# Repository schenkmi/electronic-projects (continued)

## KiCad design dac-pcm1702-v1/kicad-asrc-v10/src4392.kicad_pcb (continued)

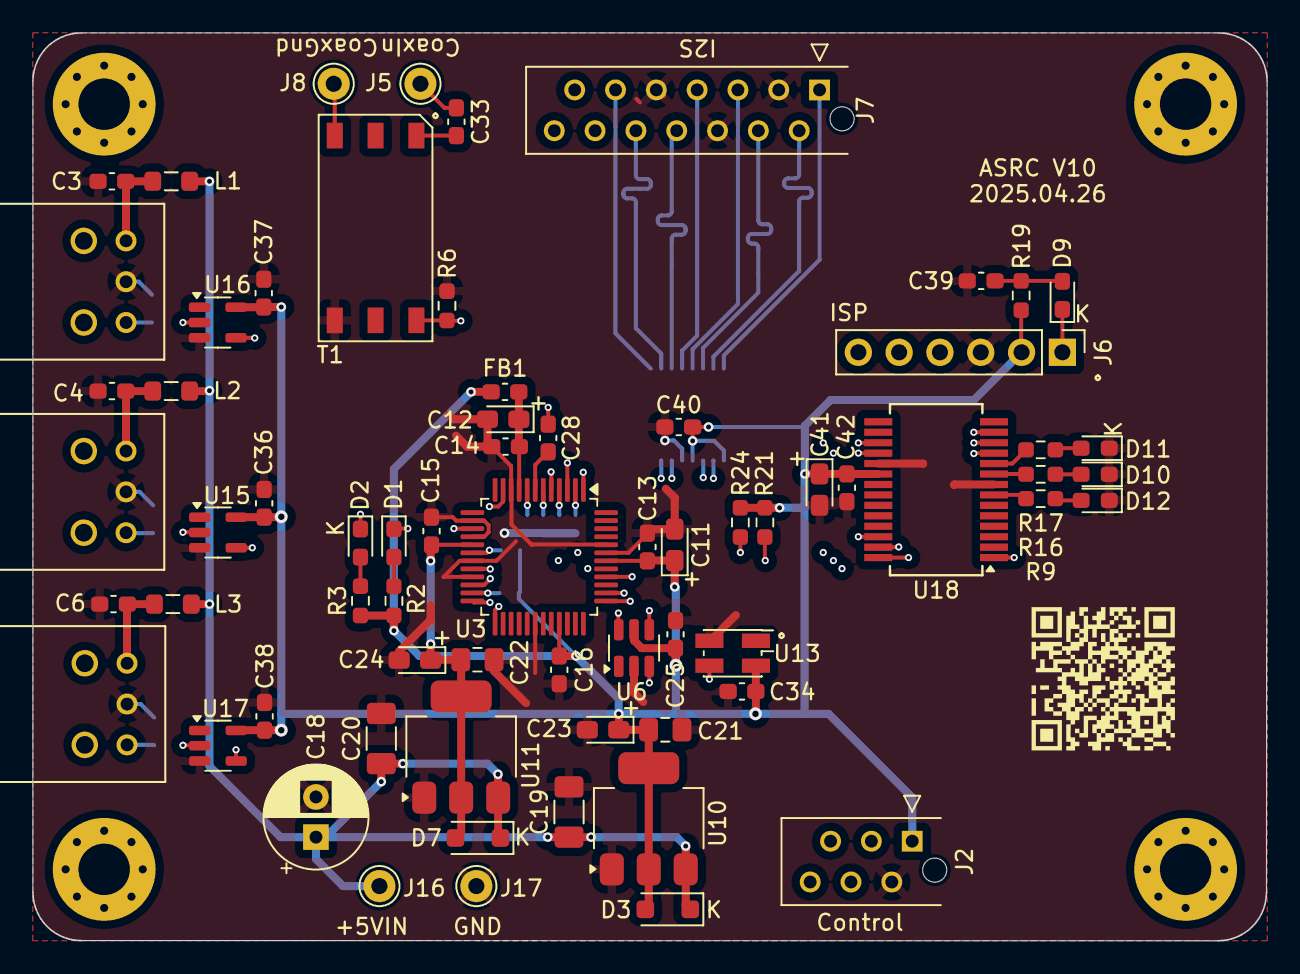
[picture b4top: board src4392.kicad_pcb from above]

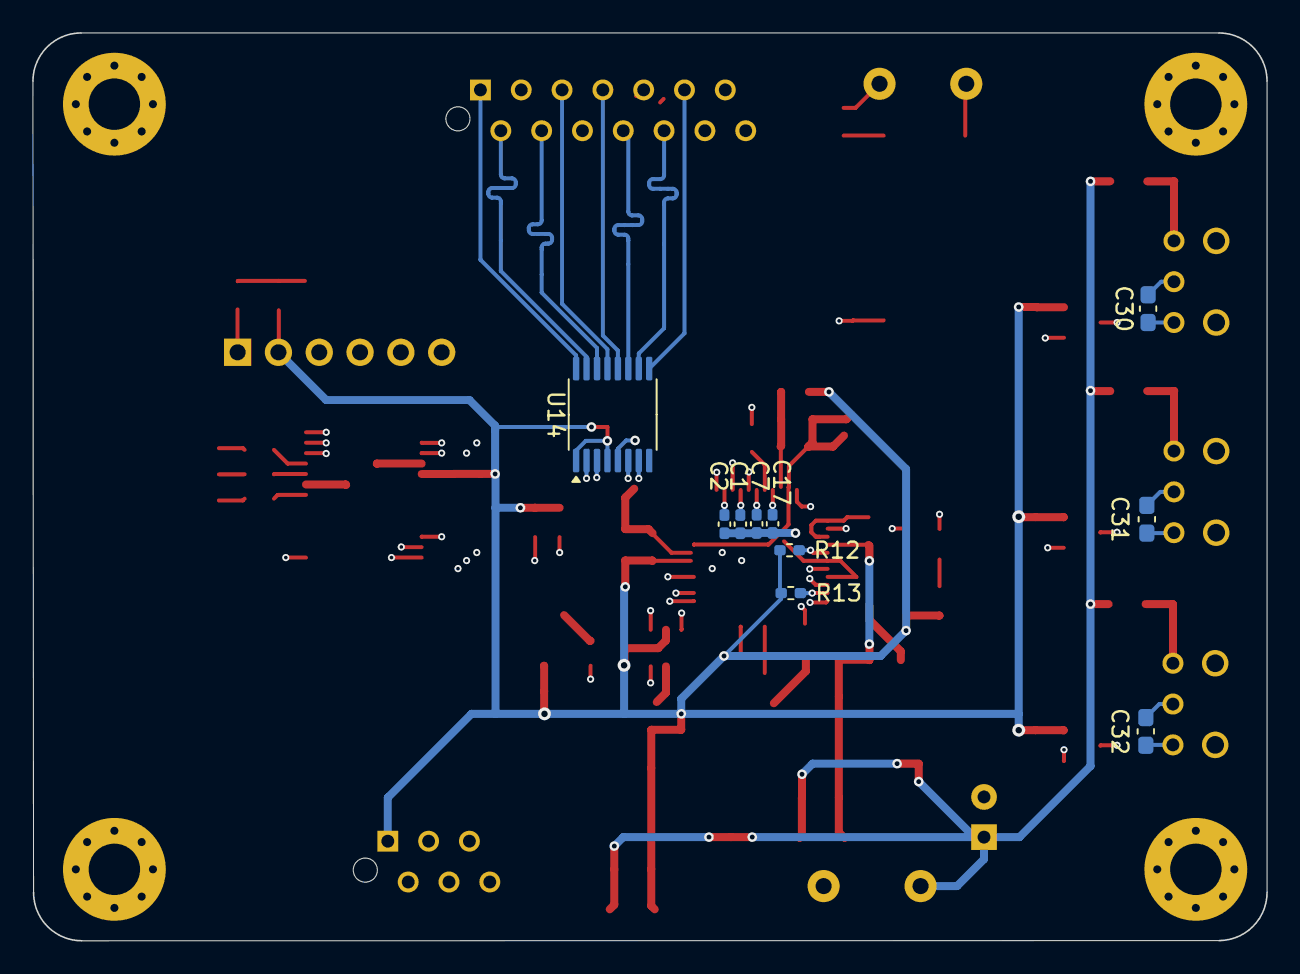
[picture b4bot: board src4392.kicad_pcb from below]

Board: 4 copper layers, 76.8 x 56.5 mm, 82 parts (10 on the bottom side), 59 nets.

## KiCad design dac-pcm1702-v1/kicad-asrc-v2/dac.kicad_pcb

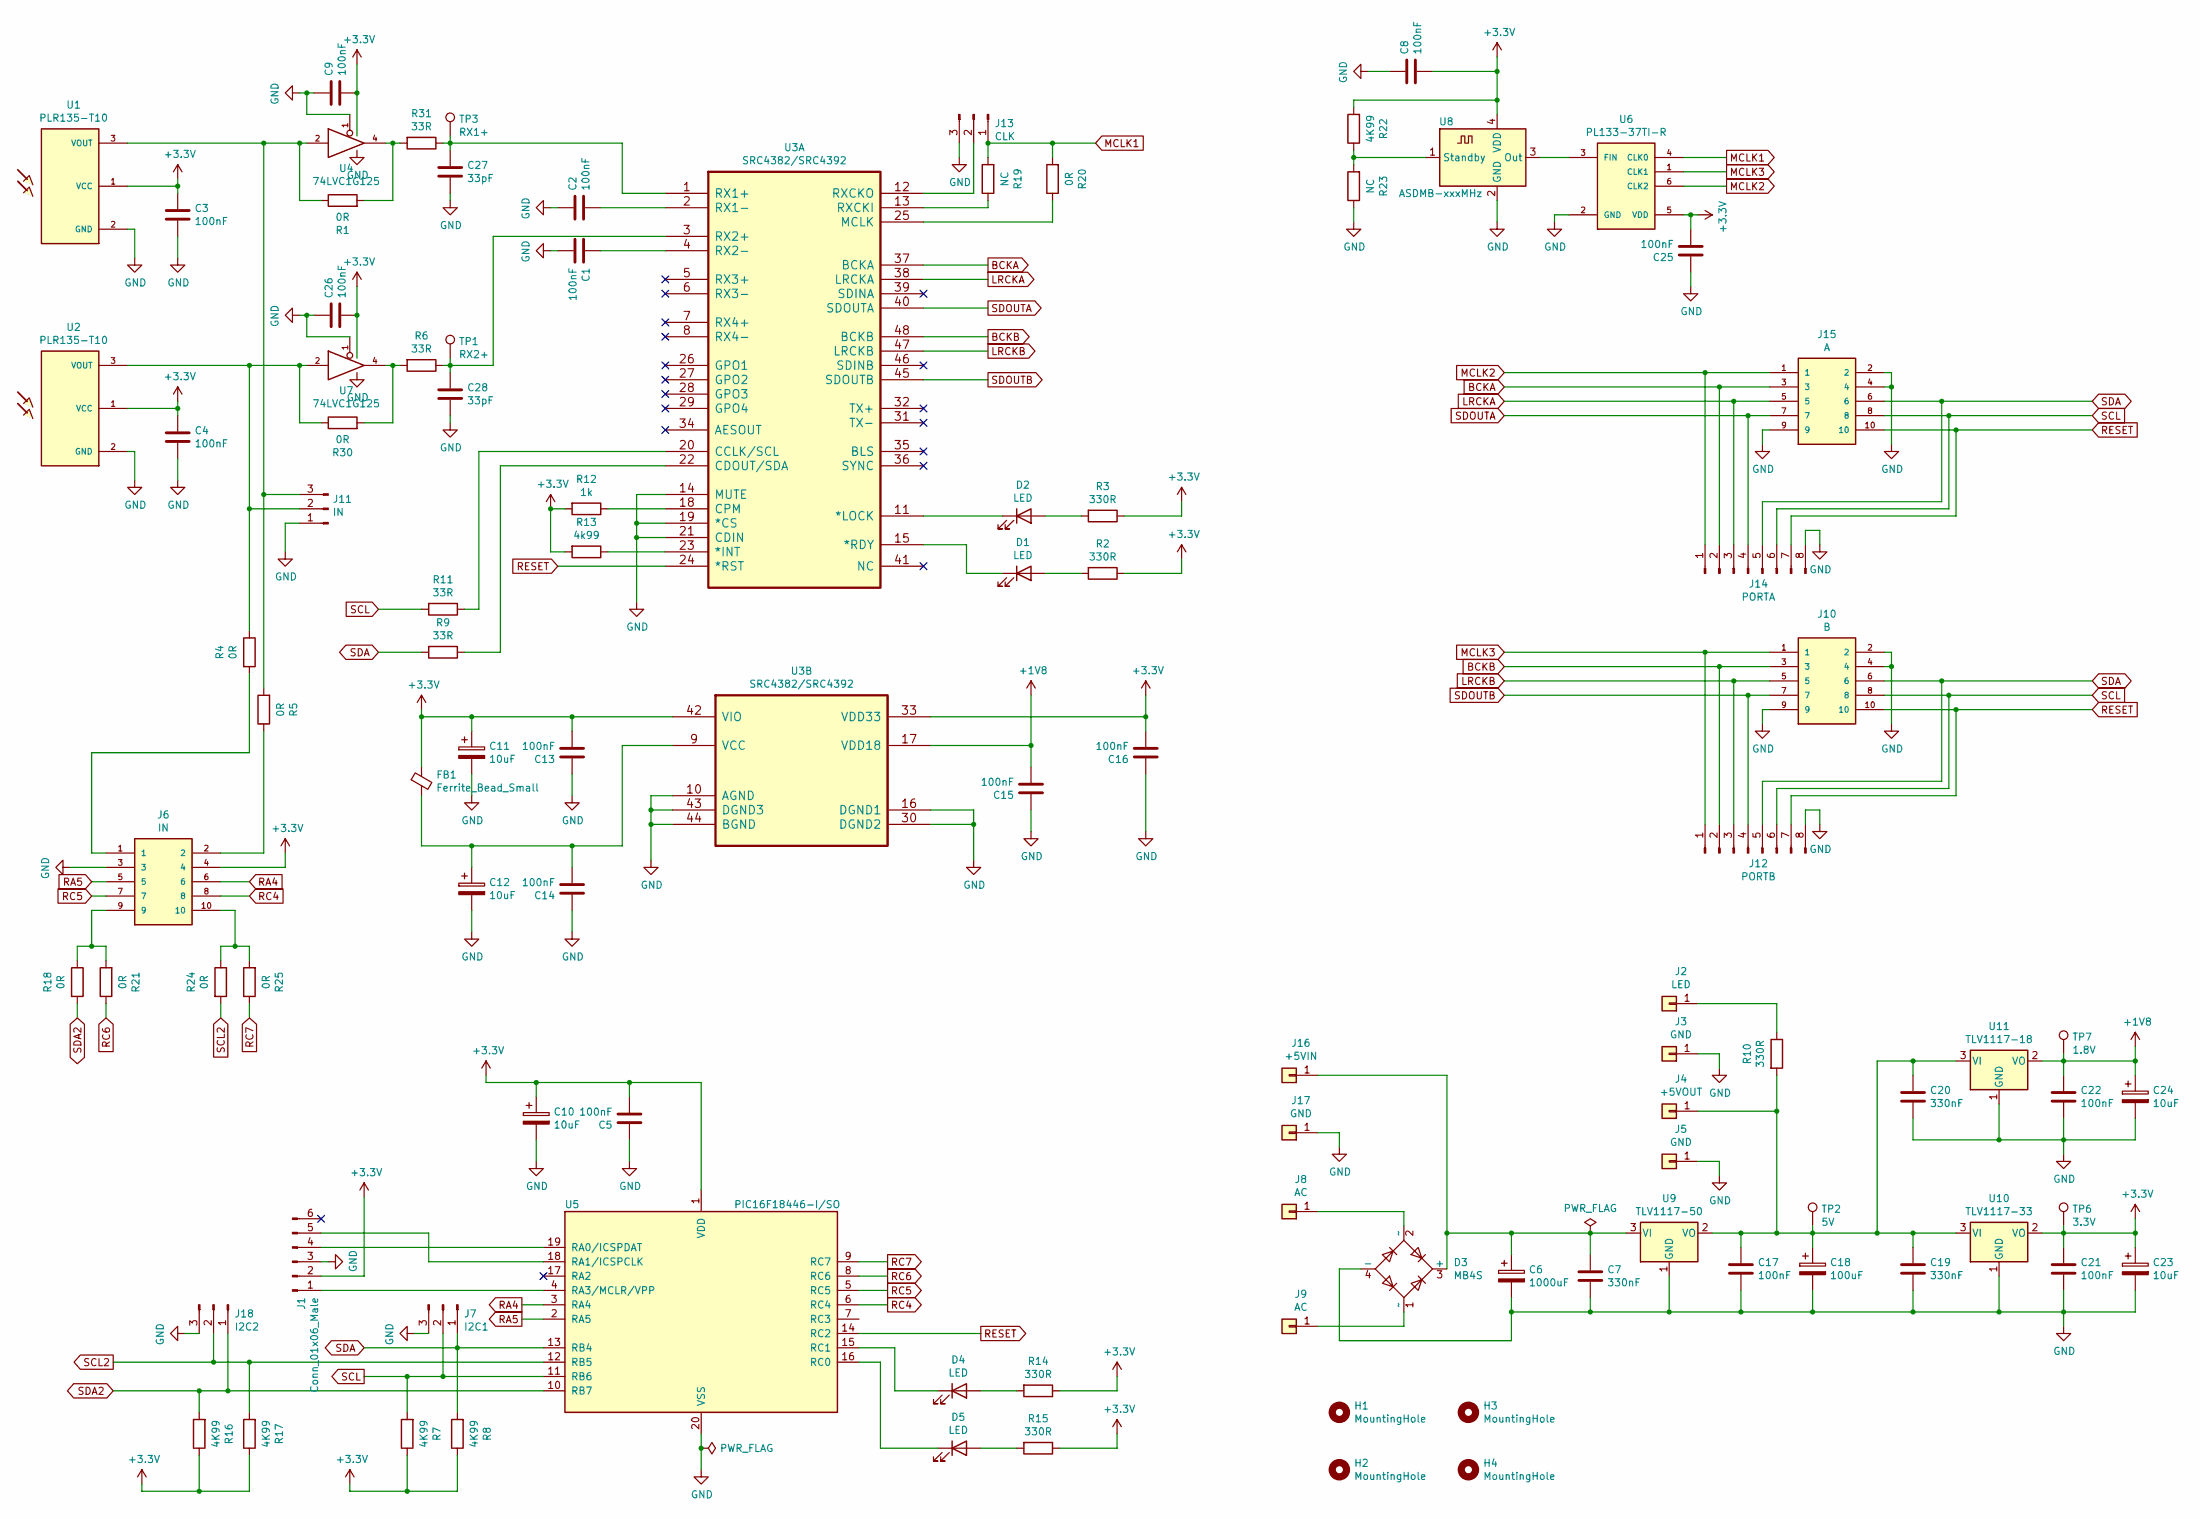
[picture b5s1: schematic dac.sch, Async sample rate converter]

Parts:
C1, C2, C3, C4, C5, C8, C9, C13, C14, C15, C16, C25, C26: 100nF; C_0603_1608Metric_Pad1.08x0.95mm_HandSolder
C6: 1000uF; CP_Radial_D12.5mm_P5.00mm
C7, C19, C20: 330nF; C_0805_2012Metric_Pad1.18x1.45mm_HandSolder
C10, C11, C12, C23, C24: 10uF; CP_EIA-3528-21_Kemet-B_Pad1.50x2.35mm_HandSolder
C17, C21, C22: 100nF; C_0805_2012Metric_Pad1.18x1.45mm_HandSolder
C18: 100uF; CP_Radial_D8.0mm_P3.50mm
C27, C28: 33pF; C_0603_1608Metric_Pad1.08x0.95mm_HandSolder
D1, D2, D4, D5: LED; LED_0805_2012Metric_Pad1.15x1.40mm_HandSolder
D3: MB4S; TO-269AA
FB1: Ferrite_Bead_Small; C_0603_1608Metric_Pad1.08x0.95mm_HandSolder
H1, H2, H3, H4: MountingHole; MountingHole_3.2mm_M3
J1: Conn_01x06_Male; PinHeader_1x06_P2.54mm_Vertical
J2: LED; Pin_D1.0mm_L10.0mm
J3, J5, J17: GND; Pin_D1.0mm_L10.0mm
J4: +5VOUT; Pin_D1.0mm_L10.0mm
J6: IN; TE_CONN_RCPT_10POS_0.1_TIN_PCB
J7: I2C1; PinHeader_1x03_P2.54mm_Vertical
J8, J9: AC; Pin_D1.0mm_L10.0mm
J10: B; TE_CONN_RCPT_10POS_0.1_TIN_PCB
J11: IN; PinHeader_1x03_P2.54mm_Vertical
J12: PORTB; PinHeader_1x08_P2.54mm_Vertical
J13: CLK; PinHeader_1x03_P2.54mm_Vertical
J14: PORTA; PinHeader_1x08_P2.54mm_Vertical
J15: A; TE_CONN_RCPT_10POS_0.1_TIN_PCB
J16: +5VIN; Pin_D1.0mm_L10.0mm
J18: I2C2; PinHeader_1x03_P2.54mm_Vertical
R1, R4, R5, R18, R20, R21, R24, R25, R30: 0R; R_0603_1608Metric_Pad0.98x0.95mm_HandSolder
R2, R3, R14, R15: 330R; R_0603_1608Metric_Pad0.98x0.95mm_HandSolder
R6, R9, R11, R31: 33R; R_0603_1608Metric_Pad0.98x0.95mm_HandSolder
R7, R8, R16, R17, R22: 4K99; R_0603_1608Metric_Pad0.98x0.95mm_HandSolder
R10: 330R; R_0805_2012Metric_Pad1.20x1.40mm_HandSolder
R12: 1k; R_0603_1608Metric_Pad0.98x0.95mm_HandSolder
R13: 4k99; R_0603_1608Metric_Pad0.98x0.95mm_HandSolder
R19, R23: NC; R_0603_1608Metric_Pad0.98x0.95mm_HandSolder
TP1: RX2+; TestPoint_Pad_D1.0mm
TP2: 5V; TestPoint_Pad_D1.0mm
TP3: RX1+; TestPoint_Pad_D1.0mm
TP6: 3.3V; TestPoint_Pad_D1.0mm
TP7: 1.8V; TestPoint_Pad_D1.0mm
U1, U2: PLR135-T10; PLR135-T10_PLT133-T10W
U3: SRC4382/SRC4392; TQFP-48_7x7mm_P0.5mm
U4, U7: 74LVC1G125; SOT-353_SC-70-5_Handsoldering
U5: PIC16F18446-I/SO; SOIC-20W_7.5x12.8mm_P1.27mm
U6: PL133-37TI-R; SOT-23-6
U8: ASDMB-xxxMHz; Oscillator_SMD_EuroQuartz_XO91-4Pin_7.0x5.0mm_HandSoldering
U9: TLV1117-50; SOT-223-3_TabPin2
U10: TLV1117-33; SOT-223-3_TabPin2
U11: TLV1117-18; SOT-223-3_TabPin2

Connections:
+1V8: C15.2, C22.1, C24.1, TP7.1, U3.17 (VDD18), U11.2 (VO)
+3V3: C3.2, C4.2, C5.2, C8.1, C9.1, C10.1, C11.1, C13.2, C16.2, C21.1, C23.1, C25.2, C26.1, FB1.1, J1.2, J6.4, R2.1, R3.1, R7.1, R8.1, R12.2, R13.2, R14.1, R15.1, R16.1, R17.1, R22.2, TP6.1, U1.1 (VCC), U2.1 (VCC), U3.33 (VDD33), U3.42 (VIO), U4.5 (VCC), U5.1 (VDD), U6.5 (VDD), U7.5 (VCC), U8.4 (VDD), U10.2 (VO)
BCKA: J14.2, J15.3, U3.37 (BCKA)
BCKB: J10.3, J12.2, U3.48 (BCKB)
GND: C1.1, C2.2, C3.1, C4.1, C5.1, C6.2, C7.2, C8.2, C9.2, C10.2, C11.2, C12.2, C13.1, C14.1, C15.1, C16.1, C17.2, C18.2, C19.2, C20.2, C21.2, C22.2, C23.2, C24.2, C25.1, C26.2, C27.1, C28.1, D3.4 (-), J1.3, J3.1, J5.1, J6.3, J7.3, J10.2, J10.4, J10.9, J11.1, J12.8, J13.3, J14.8, J15.2, J15.4, J15.9, J17.1, J18.3, R23.1, U1.2 (GND), U2.2 (GND), U3.10 (AGND), U3.14 (MUTE), U3.16 (DGND1), U3.19 (*CS), U3.21 (CDIN), U3.30 (DGND2), U3.43 (DGND3), U3.44 (BGND), U4.1, U4.3 (GND), U5.20 (VSS), U6.2 (GND), U7.1, U7.3 (GND), U8.2 (GND), U9.1 (GND), U10.1 (GND), U11.1 (GND)
LRCKA: J14.3, J15.5, U3.38 (LRCKA)
LRCKB: J10.5, J12.3, U3.47 (LRCKB)
MCLK1: J13.1, R19.2, R20.2, U6.4 (CLK0)
MCLK2: J14.1, J15.1, U6.6 (CLK2)
MCLK3: J10.1, J12.1, U6.1 (CLK1)
unnamed: C1.2, U3.4 (RX2-)
unnamed: C2.1, U3.2 (RX1-)
unnamed: C6.1, C7.1, D3.3 (+), J16.1, U9.3 (VI)
unnamed: C12.1, C14.2, FB1.2, U3.9 (VCC)
unnamed: C17.1, C18.1, C19.1, C20.1, J4.1, R10.2, TP2.1, U9.2 (VO), U10.3 (VI), U11.3 (VI)
unnamed: C27.2, R31.1, TP3.1, U3.1 (RX1+)
unnamed: C28.2, R6.1, TP1.1, U3.3 (RX2+)
unnamed: D1.1 (K), U3.15 (*RDY)
unnamed: D1.2 (A), R2.2
unnamed: D2.1 (K), U3.11 (*LOCK)
unnamed: D2.2 (A), R3.2
unnamed: D3.1 (~~), J9.1
unnamed: D3.2 (~~), J8.1
unnamed: D4.1 (K), U5.15 (RC1)
unnamed: D4.2 (A), R14.2
unnamed: D5.1 (K), U5.16 (RC0)
unnamed: D5.2 (A), R15.2
unnamed: J1.1, U5.4 (RA3/MCLR/VPP)
unnamed: J1.4, U5.19 (RA0/ICSPDAT)
unnamed: J1.5, U5.18 (RA1/ICSPCLK)
unnamed: J2.1, R10.1
unnamed: J6.1, R4.2
unnamed: J6.2, R5.1
unnamed: J6.9, R18.1, R21.2
unnamed: J6.10, R24.1, R25.2
unnamed: J11.2, R4.1, R30.1, U2.3 (VOUT), U7.2
unnamed: J11.3, R1.1, R5.2, U1.3 (VOUT), U4.2
unnamed: J13.2, U3.12 (RXCKO)
unnamed: R1.2, R31.2, U4.4
unnamed: R9.1, U3.22 (CDOUT/SDA)
unnamed: R11.1, U3.20 (CCLK/SCL)
unnamed: R12.1, U3.18 (CPM)
unnamed: R13.1, U3.23 (*INT)
unnamed: R19.1, U3.13 (RXCKI)
unnamed: R20.1, U3.25 (MCLK)
unnamed: R22.1, R23.2, U8.1 (Standby)
unnamed: R6.2, R30.2, U7.4
unnamed: U6.3 (FIN), U8.3 (Out)
RA4: J6.6, U5.3 (RA4)
RA5: J6.5, U5.2 (RA5)
RC4: J6.8, U5.6 (RC4)
RC5: J6.7, U5.5 (RC5)
RC6: R21.1, U5.8 (RC6)
RC7: R25.1, U5.9 (RC7)
RESET: J10.10, J12.7, J14.7, J15.10, U3.24 (*RST), U5.14 (RC2)
SCL: J7.2, J10.8, J12.6, J14.6, J15.8, R7.2, R11.2, U5.11 (RB6)
SCL2: J18.2, R17.2, R24.2, U5.12 (RB5)
SDA: J7.1, J10.6, J12.5, J14.5, J15.6, R8.2, R9.2, U5.13 (RB4)
SDA2: J18.1, R16.2, R18.2, U5.10 (RB7)
SDOUTA: J14.4, J15.7, U3.40 (SDOUTA)
SDOUTB: J10.7, J12.4, U3.45 (SDOUTB)

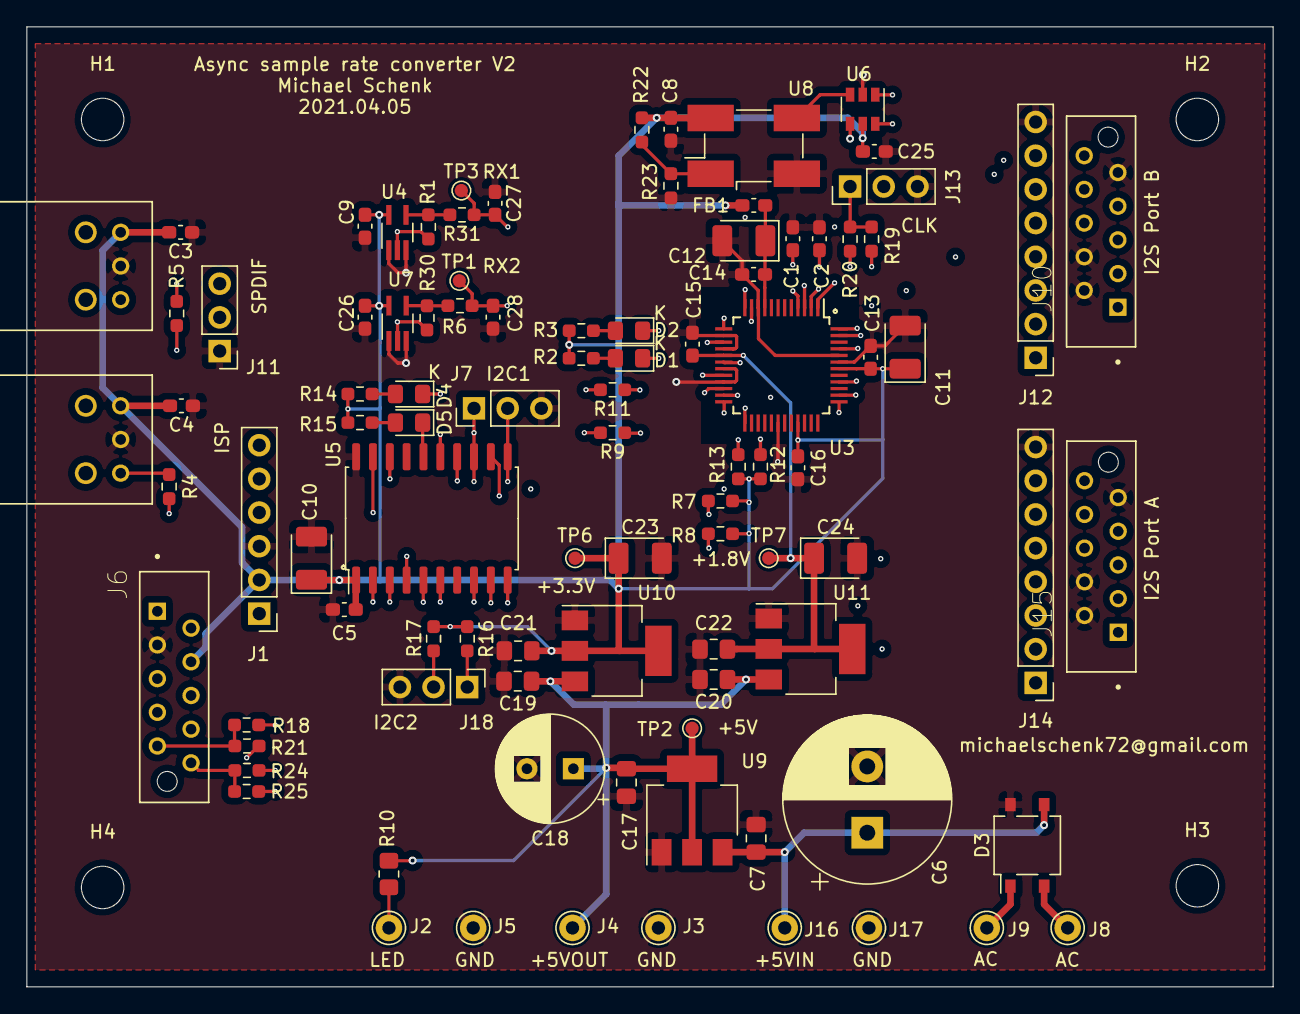
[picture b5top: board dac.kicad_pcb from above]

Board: 4 copper layers, 94.0 x 72.4 mm, 99 parts (0 on the bottom side), 61 nets.
